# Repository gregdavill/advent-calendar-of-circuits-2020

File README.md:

# Advent Calendar of Circuits 2020 #

## What is it?
The challenge is to design an average of 1 circuit board design and layout per day for 31 days in December.

## Designs

  1. [__gdpi__](gpdi/) SYZYGY pod featuring 2x digital video ports
  2. [__resonance__](resonance/) Addon board for card10 to add video output
  3. [__meiji-led-ring__](meiji-led-ring/) Illuminator to fit around the front of a microscope
  4. [__pcie_x4__](pcie_x4/) SYZYGY pod creating a PCIe x4 add-in card
  5. [__icebreaker++__](icebreaker++/) icebreaker FPGA board, upgraded with an ECP5
  6. [__pcie_x1__](pcie_x1/) SYZYGY pod creating a compact PCIe x1 add-in card
  7. [__arm-watch__](arm-watch/) New ARM based controller for the Casio CA-53W watch
  8. [__syzygy-sgmii__](syzygy-sgmii/) Gigabit ethernet using an SGMII based PHY
  9. [__hdmi-si__](hdmi-si/) HDMI breakout board
  10. [__quad-7segment__](pmod-quad-7segment/) PMOD with a quad 7segment
  11. [__syzygy-breakout__](syzygy-breakout/) Breakout board for a standard SYZYGY connector
  12. [__icebreaker++-ram__](icebreaker++-ram/) icebreaker FPGA board, upgraded with an ECP5 (+extra RAM)
  13. [__sd-dummy__](pmod-sd-dummy/) Dummy SD card to connect to a host system via SDIO
  14. [__gpdi-serdes__](gpdi-serdes/) GPDI using the serdes
  15. [__rpi-hq-camera__](rpi-hq-camera/) Connector for the Raspberry Pi HQ camera
  16. [__syzygy-pmod__](syzygy-pmod/) SYZYGY to PMOD adapter
  17. [__pmod-gnss__](pmod-gnss/) GNSS PMOD, GPS + Glonass
  18. [__led-panel__](led-panel/) Breakout for some White LEDs
  19. [__syzygy-txr-breakout__](syzygy-txr-breakout/) SYZYGY TXR4 to SMA connectors
  20. [__syzygy-dual-atto320__](syzygy-dual-atto320/) SYZYGY to dual Atto320 LWIR sensors
  21. [__syzygy-rgb888-lcd__](syzygy-rgb888-lcd/) SYZYGY 5" 800x480 LCD panel
  22. [__memory-lcd-wing__](memory-lcd-wing/) minimal wing for OrangeCrab
  23. [__syzygy-flir-tau2__](syzygy-flir-tau2/) SYZYGY tau2 LWIR core
  24. [__syzygy-flir-boson__](syzygy-flir-boson/) SYZYGY boson LWIR core
  25. [__SCD30-3d-model__](SCD30-3d-model/) 3d model for the SCD30 CO2 Sensor
  26. [__esp32s2-co2-monitor__](esp32s2-co2-monitor/) ESP32s2 + Sharp memory LCD + CO2 Monitor
  27. [__jtag-programmer__](jtag-programmer/) FT232H based JTAG programmer
  28. [__ECPBreaker__](ecpbreaker/) ECP5 based icebreaker update, FX2 HS USB + SYZYGY
  29. [__esp32s2-lepton__](esp32s2-lepton/) Small ESP32 based thermal camera
  30. [__esp32s2-breakout__](esp32s2-breakout/) ESP32S2 + Sharp memory LCD
  31. [__syzygy-epc901__](syzygy-epc901/) SYZYGY breakout with an EPC901 CCD + 50MSps ADC

## Licence
 * Unless otherwise indicated hardware in this repository is licensed under CERN-OHL-P-2.0

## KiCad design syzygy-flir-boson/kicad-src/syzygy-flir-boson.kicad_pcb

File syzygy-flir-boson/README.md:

# SYZYGY FLIR Boson 

SYZYGY is an FPGA expansion standard for medium to high speed interfaces. Learn more and check out the specifications here: [https://syzygyfpga.io/](https://syzygyfpga.io/)

---

## What is it

An addon for the boson LWIR core from FLIR. 
The 24bit CMOS channel is connected through to the SYZYGY connector along with the UART configuration channel.

## Folder structure

```
kicad-src: KiCad v6 source files
production:
 - Gerbers:      [project]_gerbers.zip
 - Schematic:    [project].pdf
 - Board render: [project].png
```

## Render

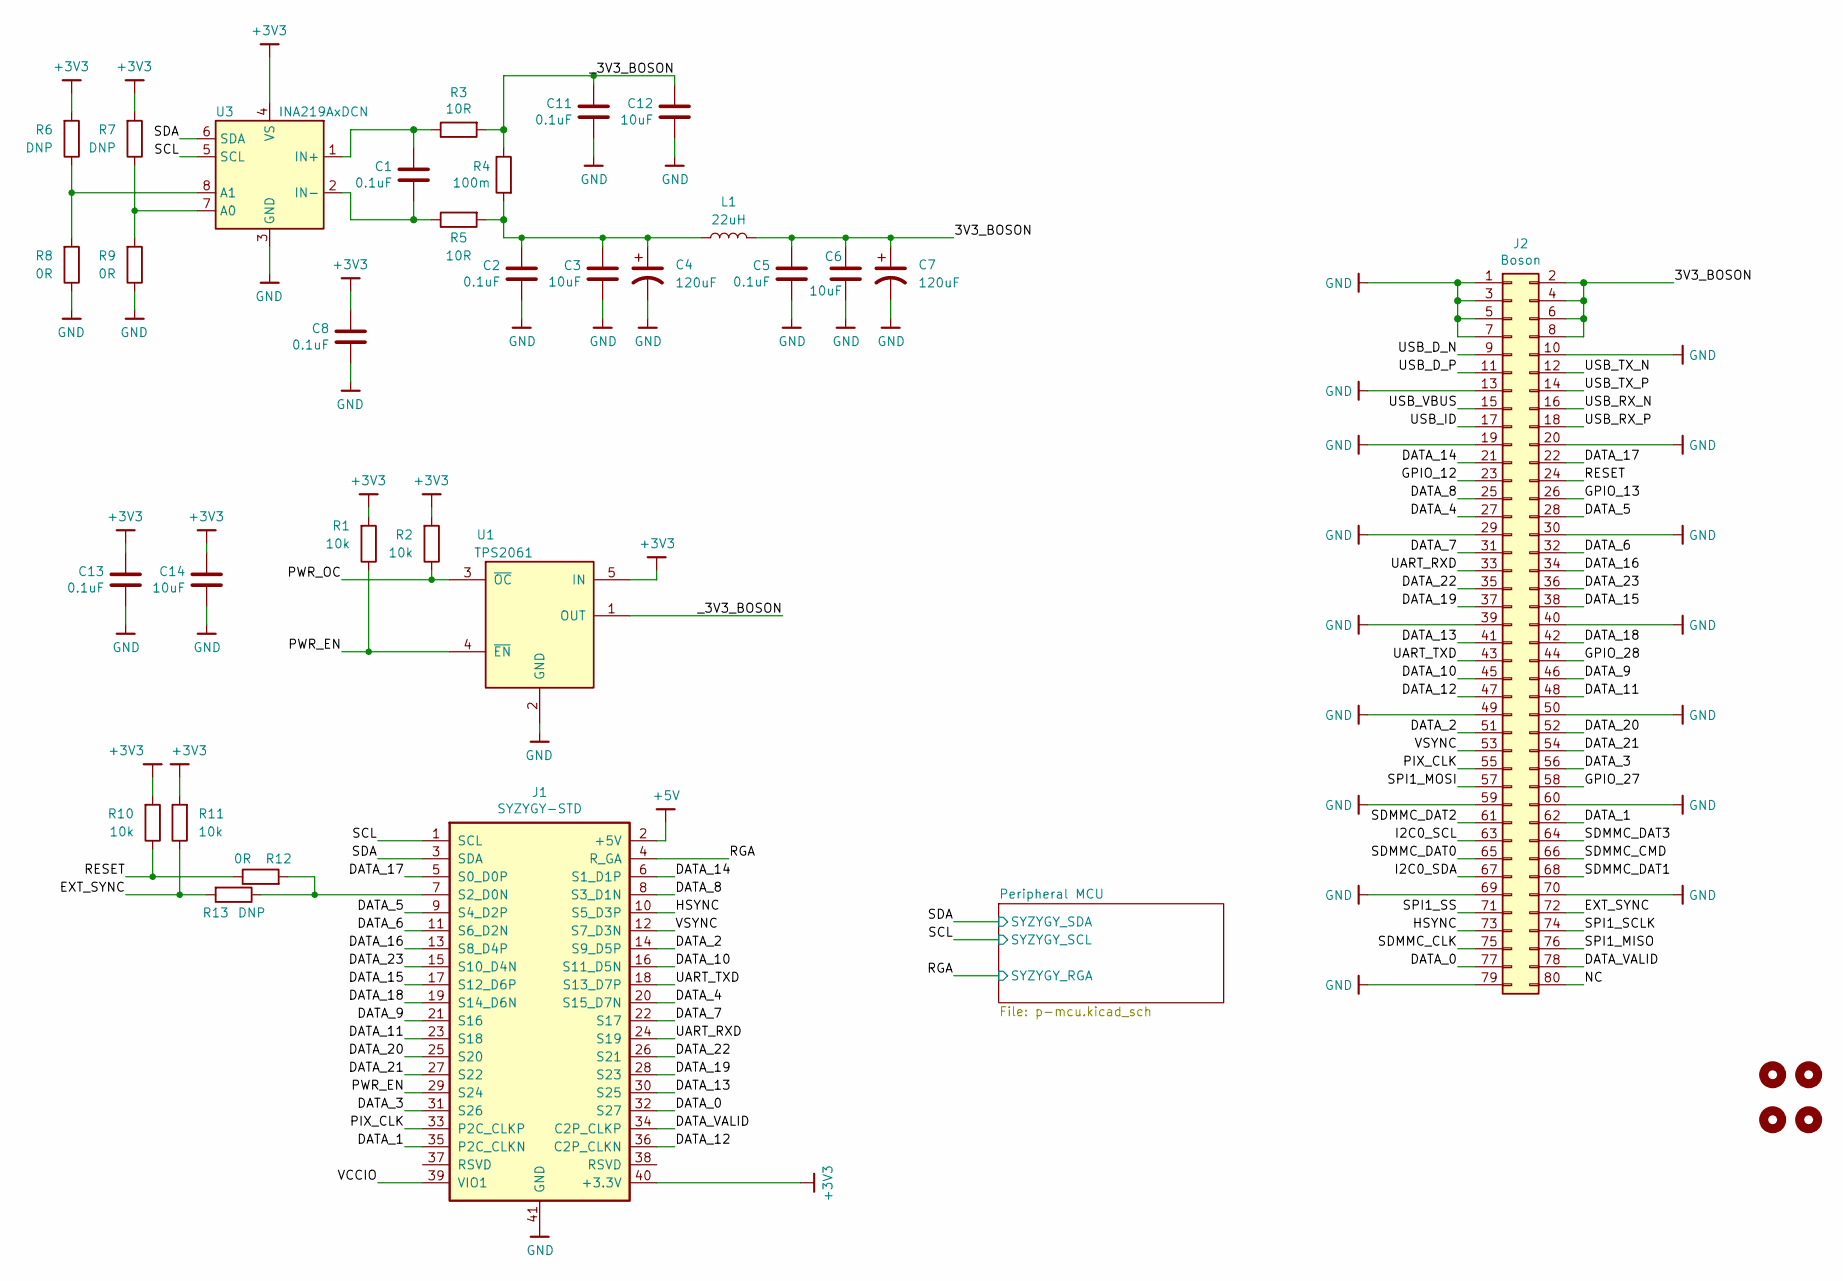
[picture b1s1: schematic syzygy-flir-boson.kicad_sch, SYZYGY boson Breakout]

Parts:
C1, C2, C5, C8, C11, C13: 0.1uF; C_0402_1005Metric
C3, C6, C12, C14: 10uF; C_0805_2012Metric
C4, C7: 120uF; CP_Elec_6.3x5.3
H1, H2, H3, H4: MountingHole; MountingHole_3.2mm_M3_DIN965
J1: SYZYGY-STD; SYZYGY-STD-POD
J2: Boson; DF40_80Pin
L1: 22uH; L_Taiyo-Yuden_NR-50xx
R1, R2, R10, R11: 10k; R_0402_1005Metric
R3, R5: 10R; R_0402_1005Metric
R4: 100m; R_0805_2012Metric
R6, R7, R13: DNP; R_0402_1005Metric
R8, R9, R12: 0R; R_0402_1005Metric
U1: TPS2061; SOT-23-5
U3: INA219AxDCN; SOT-23-8

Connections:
+3V3: C8.1, C13.1, C14.1, J1.40 (+3.3V), R1.2, R2.2, R6.2, R7.2, R10.2, R11.2, U1.5 (IN), U3.4 (VS); also elsewhere on the board
+5V: J1.2 (+5V)
/3V3_BOSON: C5.1, C6.1, C7.1, J2.2, J2.4, J2.6, J2.8, L1.2
/DATA_0: J1.32 (S27), J2.77
/DATA_1: J1.35 (P2C_CLKN), J2.62
/DATA_2: J1.14 (S9_D5P), J2.51
/DATA_3: J1.31 (S26), J2.56
/DATA_4: J1.20 (S15_D7N), J2.27
/DATA_5: J1.9 (S4_D2P), J2.28
/DATA_6: J1.11 (S6_D2N), J2.32
/DATA_7: J1.22 (S17), J2.31
/DATA_8: J1.8 (S3_D1N), J2.25
/DATA_9: J1.21 (S16), J2.46
/DATA_10: J1.16 (S11_D5N), J2.45
/DATA_11: J1.23 (S18), J2.48
/DATA_12: J1.36 (C2P_CLKN), J2.47
/DATA_13: J1.30 (S25), J2.41
/DATA_14: J1.6 (S1_D1P), J2.21
/DATA_15: J1.17 (S12_D6P), J2.38
/DATA_16: J1.13 (S8_D4P), J2.34
/DATA_17: J1.5 (S0_D0P), J2.22
/DATA_18: J1.19 (S14_D6N), J2.42
/DATA_19: J1.28 (S23), J2.37
/DATA_20: J1.25 (S20), J2.52
/DATA_21: J1.27 (S22), J2.54
/DATA_22: J1.26 (S21), J2.35
/DATA_23: J1.15 (S10_D4N), J2.36
/DATA_VALID: J1.34 (C2P_CLKP), J2.78
/EXT_SYNC: J2.72, R11.1, R13.2
/GPIO_12: J2.23
/GPIO_13: J2.26
/GPIO_27: J2.58
/GPIO_28: J2.44
/HSYNC: J1.10 (S5_D3P), J2.73
/I2C0_SCL: J2.63
/I2C0_SDA: J2.67
/NC: J2.80
/PIX_CLK: J1.33 (P2C_CLKP), J2.55
/PWR_EN: J1.29 (S24), R1.1, U1.4 (~EN)
/PWR_OC: R2.1, U1.3 (~OC)
/RESET: J2.24, R10.1, R12.1
/RGA: J1.4 (R_GA); also elsewhere on the board
/SCL: J1.1 (SCL), U3.5 (SCL); also elsewhere on the board
/SDA: J1.3 (SDA), U3.6 (SDA); also elsewhere on the board
/SDMMC_CLK: J2.75
/SDMMC_CMD: J2.66
/SDMMC_DAT0: J2.65
/SDMMC_DAT1: J2.68
/SDMMC_DAT2: J2.61
/SDMMC_DAT3: J2.64
/SPI1_MISO: J2.76
/SPI1_MOSI: J2.57
/SPI1_SCLK: J2.74
/SPI1_SS: J2.71
/UART_RXD: J1.24 (S19), J2.33
/UART_TXD: J1.18 (S13_D7P), J2.43
/USB_D_N: J2.9
/USB_D_P: J2.11
/USB_ID: J2.17
/USB_RX_N: J2.16
/USB_RX_P: J2.18
/USB_TX_N: J2.12
/USB_TX_P: J2.14
/USB_VBUS: J2.15
/VCCIO: J1.39 (VIO1)
/VSYNC: J1.12 (S7_D3N), J2.53
/_3V3_BOSON: C11.1, C12.1, R3.2, R4.1, U1.1 (OUT)
GND: C2.2, C3.2, C4.2, C5.2, C6.2, C7.2, C8.2, C11.2, C12.2, C13.2, C14.2, J1.41 (GND), J2.1, J2.3, J2.5, J2.7, J2.10, J2.13, J2.19, J2.20, J2.29, J2.30, J2.39, J2.40, J2.49, J2.50, J2.59, J2.60, J2.69, J2.70, J2.79, R8.1, R9.1, U1.2 (GND), U3.3 (GND); also elsewhere on the board
unnamed: C1.1, R3.1, U3.1 (IN+)
unnamed: C1.2, R5.1, U3.2 (IN-)
unnamed: C2.1, C3.1, C4.1, L1.1, R4.2, R5.2
unnamed: J1.7 (S2_D0N), R12.2, R13.1
unnamed: R6.1, R8.2, U3.8 (A1)
unnamed: R7.1, R9.2, U3.7 (A0)

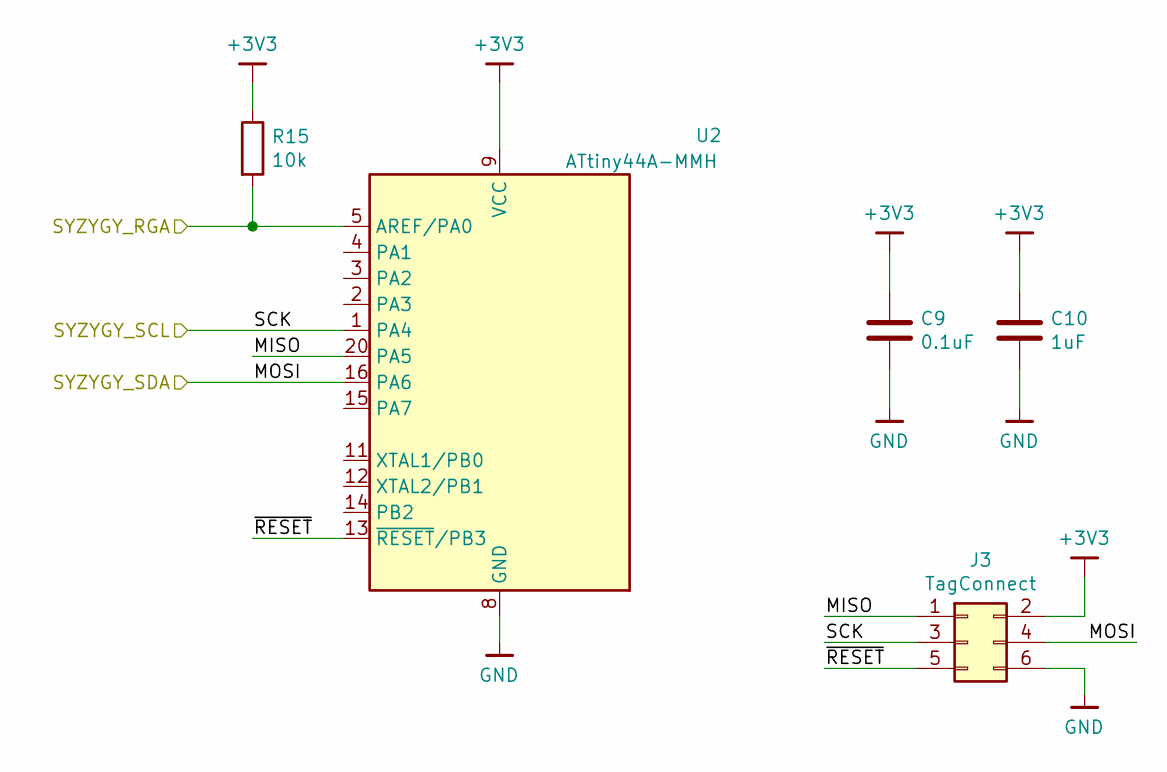
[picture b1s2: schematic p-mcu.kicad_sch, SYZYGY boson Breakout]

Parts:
C9: 0.1uF; C_0402_1005Metric
C10: 1uF; C_0402_1005Metric
J3: TagConnect; TC2030-NL_SMALL
R15: 10k; R_0402_1005Metric
U2: ATtiny44A-MMH; QFN-20-1EP_3x3mm_P0.45mm_EP1.6x1.6mm

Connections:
+3V3: C9.1, C10.1, J3.2, R15.1, U2.9 (VCC); also elsewhere on the board
/Peripheral MCU/MISO: J3.1, U2.20 (PA5)
/Peripheral MCU/~RESET: J3.5, U2.13 (~RESET~/PB3)
/RGA: R15.2, U2.5 (AREF/PA0); also elsewhere on the board
/SCL: J3.3, U2.1 (PA4); also elsewhere on the board
/SDA: J3.4, U2.16 (PA6); also elsewhere on the board
GND: C9.2, C10.2, J3.6, U2.8 (GND), U2.21 (GND); also elsewhere on the board

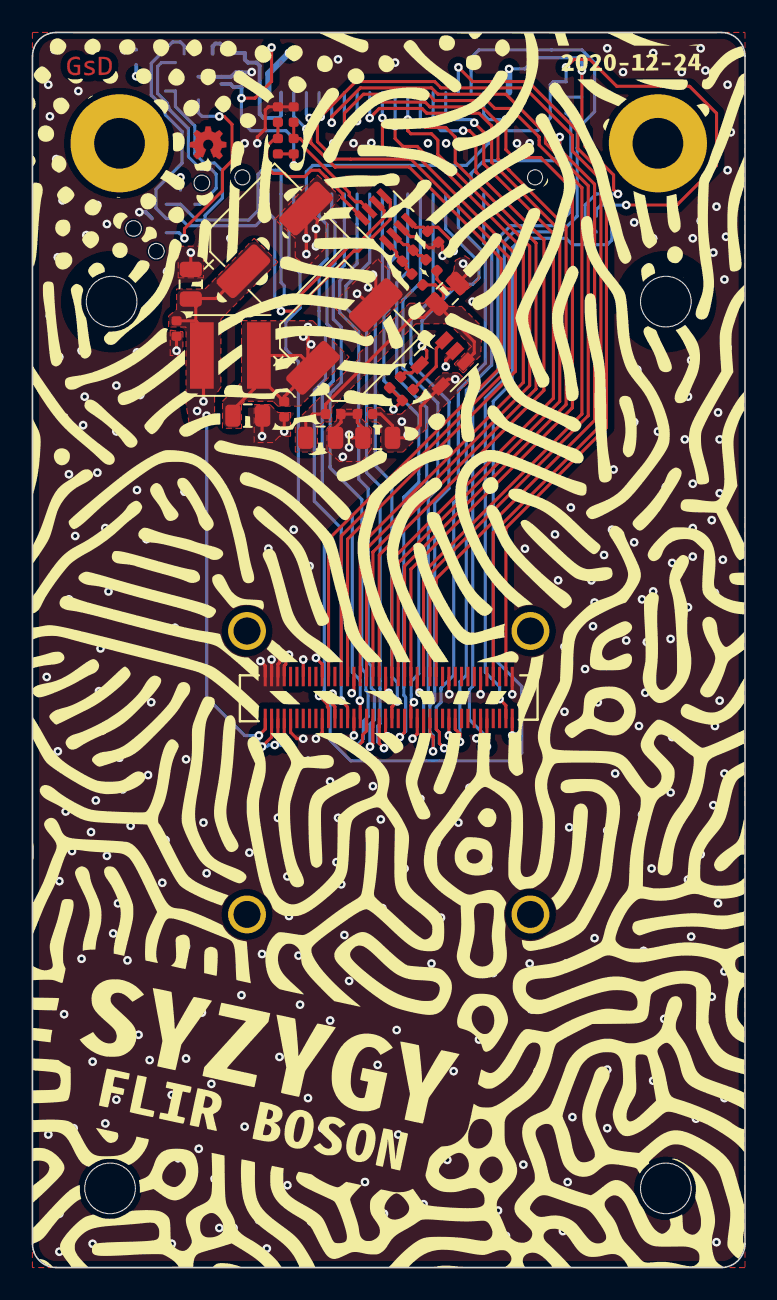
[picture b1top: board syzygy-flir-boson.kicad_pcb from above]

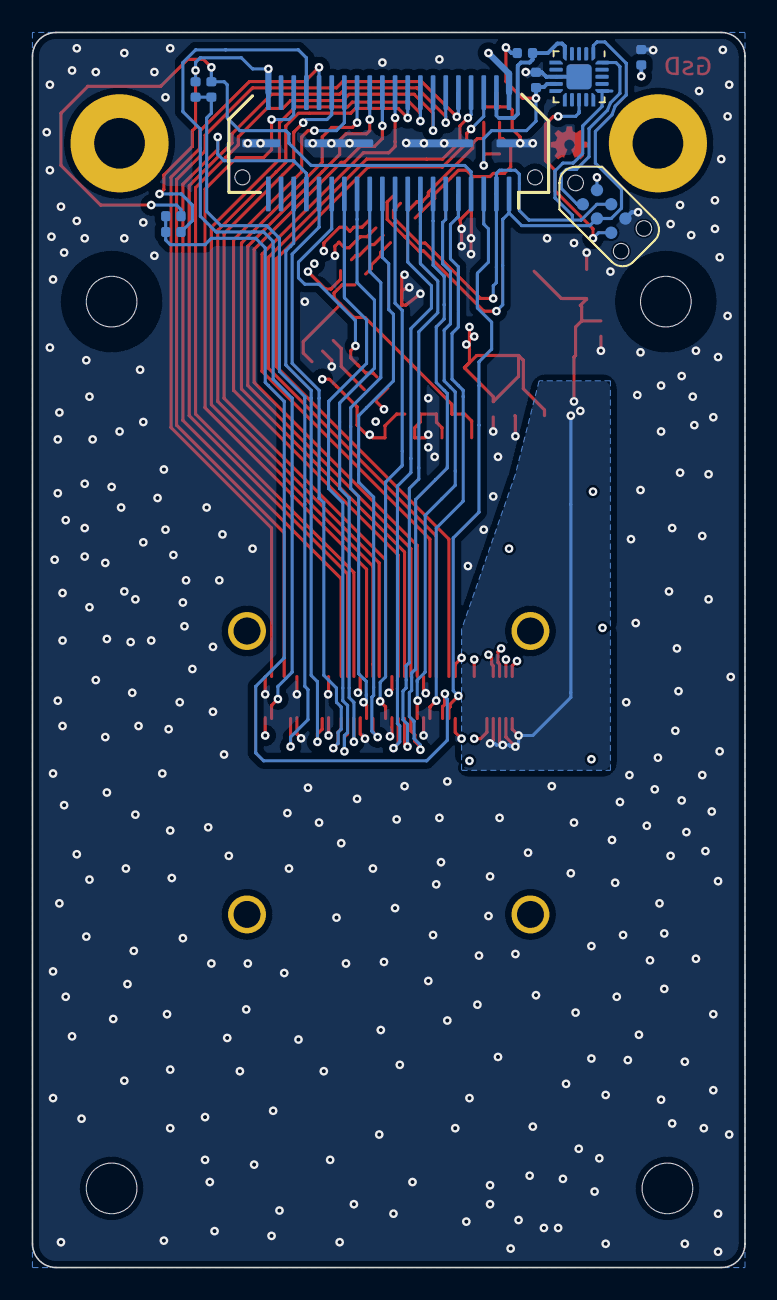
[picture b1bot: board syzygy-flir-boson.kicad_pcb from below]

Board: 4 copper layers, 45.0 x 78.0 mm, 43 parts (10 on the bottom side), 49 nets.

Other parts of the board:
H1#2: MountingHole; MountingHole_3.2mm_M3_DIN965
H1#3, H1#4, H1#5: MountingHole; Pin_D1.0mm_L10.0mm

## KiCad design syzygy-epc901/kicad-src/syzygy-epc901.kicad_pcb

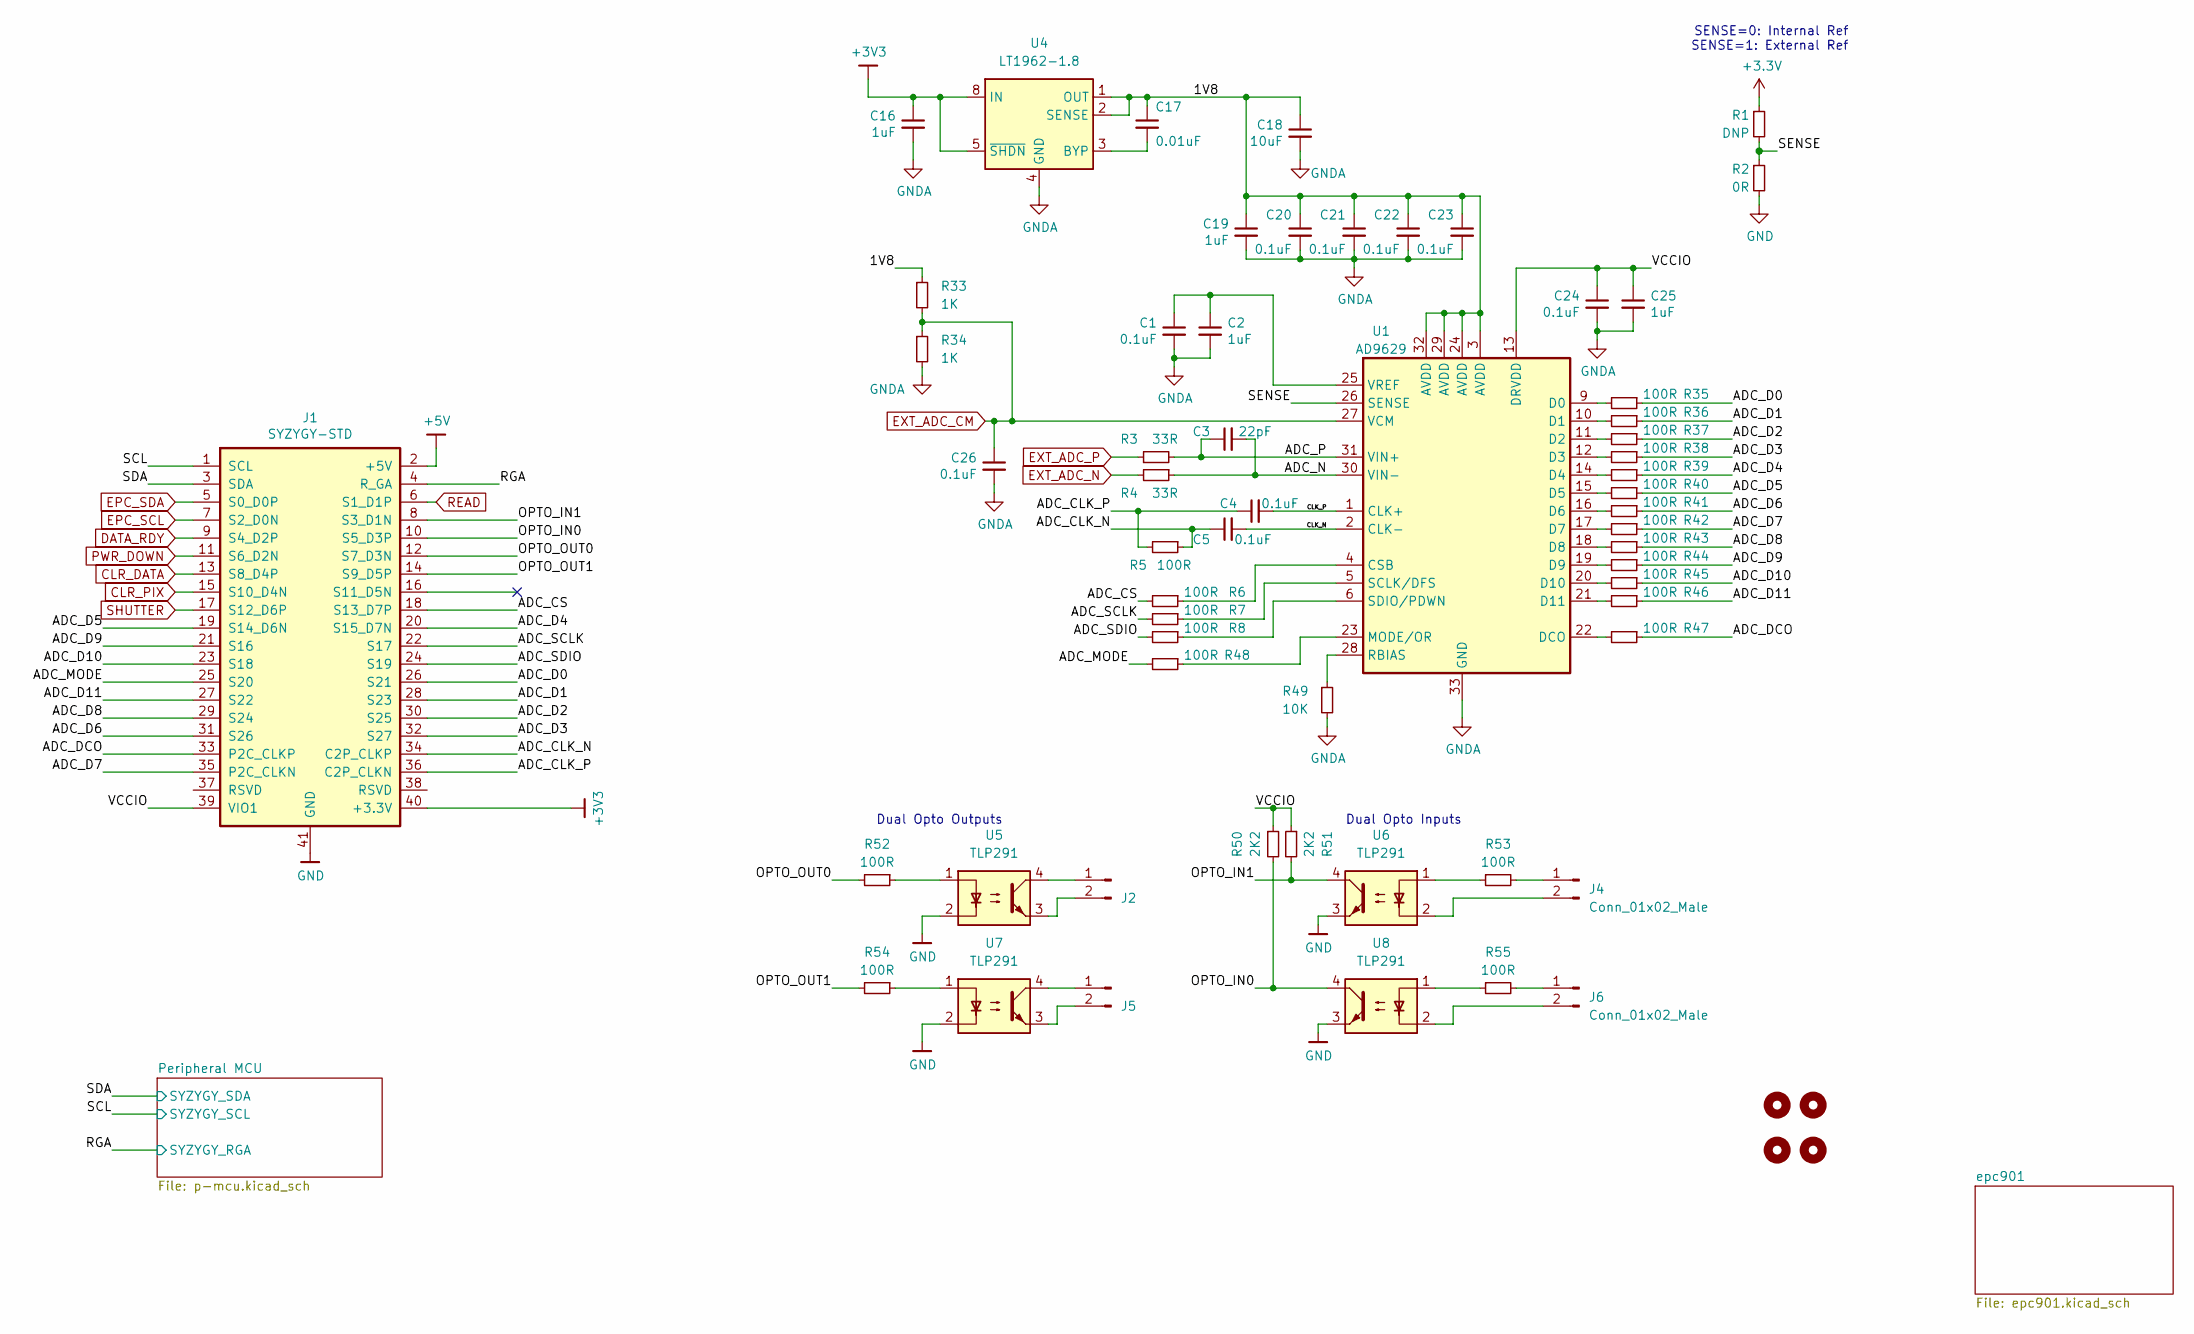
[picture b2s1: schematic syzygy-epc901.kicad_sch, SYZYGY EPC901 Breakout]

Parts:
C1, C4, C5, C20, C21, C22, C23, C24, C26: 0.1uF; C_0402_1005Metric
C2, C16, C19, C25: 1uF; C_0402_1005Metric
C3: 22pF; C_0402_1005Metric
C17: 0.01uF; C_0402_1005Metric
C18: 10uF; C_0603_1608Metric
H1, H2, H3, H4: MountingHole; MountingHole_3.2mm_M3_DIN965
J1: SYZYGY-STD; SYZYGY-STD-POD
J2, J4, J5, J6: Conn_01x02_Male; PinHeader_1x02_P2.54mm_Vertical
R1: DNP; R_0402_1005Metric
R2: 0R; R_0402_1005Metric
R3, R4: 33R; R_0402_1005Metric
R5, R6, R7, R8, R35, R36, R37, R38, R39, R40, R41, R42, R43, R44, R45, R46, R47, R48, R52, R53, R54, R55: 100R; R_0402_1005Metric
R33, R34: 1K; R_0402_1005Metric
R49: 10K; R_0402_1005Metric
R50, R51: 2K2; R_0402_1005Metric
U1: AD9629; QFN-32-1EP_5x5mm_P0.5mm_EP3.6x3.6mm_ThermalVias
U4: LT1962-1.8; MSOP-8_3x3mm_P0.65mm
U5, U6, U7, U8: TLP291; SOIC-4_4.55x2.6mm_P1.27mm

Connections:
+5V: J1.2 (+5V)
/1V8: C17.1, C18.1, C19.1, C20.1, C21.1, C22.1, C23.1, R33.1, U1.3 (AVDD), U1.24 (AVDD), U1.29 (AVDD), U1.32 (AVDD), U4.1 (OUT), U4.2 (SENSE)
/ADC_CLK_N: C5.1, J1.34 (C2P_CLKP), R5.1
/ADC_CLK_P: C4.1, J1.36 (C2P_CLKN), R5.2
/ADC_CS: J1.18 (S13_D7P), R6.2
/ADC_D0: J1.26 (S21), R35.1
/ADC_D1: J1.28 (S23), R36.1
/ADC_D2: J1.30 (S25), R37.1
/ADC_D3: J1.32 (S27), R38.1
/ADC_D4: J1.20 (S15_D7N), R39.1
/ADC_D5: J1.19 (S14_D6N), R40.1
/ADC_D6: J1.31 (S26), R41.1
/ADC_D7: J1.35 (P2C_CLKN), R42.1
/ADC_D8: J1.29 (S24), R43.1
/ADC_D9: J1.21 (S16), R44.1
/ADC_D10: J1.23 (S18), R45.1
/ADC_D11: J1.27 (S22), R46.1
/ADC_DCO: J1.33 (P2C_CLKP), R47.1
/ADC_MODE: J1.25 (S20), R48.2
/ADC_N: C3.2, R4.1, U1.30 (VIN-)
/ADC_P: C3.1, R3.2, U1.31 (VIN+)
/ADC_SCLK: J1.22 (S17), R7.2
/ADC_SDIO: J1.24 (S19), R8.2
/CLK_N: C5.2, U1.2 (CLK-)
/CLK_P: C4.2, U1.1 (CLK+)
/OPTO_IN0: J1.10 (S5_D3P), R50.2, U8.4
/OPTO_IN1: J1.8 (S3_D1N), R51.2, U6.4
/OPTO_OUT0: J1.12 (S7_D3N), R52.2
/OPTO_OUT1: J1.14 (S9_D5P), R54.2
/RGA: J1.4 (R_GA); also elsewhere on the board
/SCL: J1.1 (SCL); also elsewhere on the board
/SDA: J1.3 (SDA); also elsewhere on the board
/SENSE: R1.2, R2.1, U1.26 (SENSE)
/VCCIO: C24.1, C25.1, J1.39 (VIO1), R50.1, R51.1, U1.13 (DRVDD)
CLR_DATA: J1.13 (S8_D4P); also elsewhere on the board
CLR_PIX: J1.15 (S10_D4N); also elsewhere on the board
DATA_RDY: J1.9 (S4_D2P); also elsewhere on the board
EPC_SCL: J1.7 (S2_D0N); also elsewhere on the board
EPC_SDA: J1.5 (S0_D0P); also elsewhere on the board
EXT_ADC_CM: C26.1, R33.2, R34.1, U1.27 (VCM); also elsewhere on the board
EXT_ADC_N: R4.2; also elsewhere on the board
EXT_ADC_P: R3.1; also elsewhere on the board
GND: C1.2, C2.2, C16.2, C18.2, C19.2, C20.2, C21.2, C22.2, C23.2, C24.2, C25.2, C26.2, J1.41 (GND), R2.2, R34.2, R49.2, U1.33 (GND), U4.4 (GND), U5.2, U6.3, U7.2, U8.3; also elsewhere on the board
unnamed: C1.1, C2.1, U1.25 (VREF)
unnamed: C17.2, U4.3 (BYP)
unnamed: J2.1, U5.4
unnamed: J2.2, U5.3
unnamed: J4.1, R53.2
unnamed: J4.2, U6.2
unnamed: J5.1, U7.4
unnamed: J5.2, U7.3
unnamed: J6.1, R55.2
unnamed: J6.2, U8.2
unnamed: R6.1, U1.4 (CSB)
unnamed: R7.1, U1.5 (SCLK/DFS)
unnamed: R8.1, U1.6 (SDIO/PDWN)
unnamed: R35.2, U1.9 (D0)
unnamed: R36.2, U1.10 (D1)
unnamed: R37.2, U1.11 (D2)
unnamed: R38.2, U1.12 (D3)
unnamed: R39.2, U1.14 (D4)
unnamed: R40.2, U1.15 (D5)
unnamed: R41.2, U1.16 (D6)
unnamed: R42.2, U1.17 (D7)
unnamed: R43.2, U1.18 (D8)
unnamed: R44.2, U1.19 (D9)
unnamed: R45.2, U1.20 (D10)
unnamed: R46.2, U1.21 (D11)
unnamed: R47.2, U1.22 (DCO)
unnamed: R48.1, U1.23 (MODE/OR)
unnamed: R49.1, U1.28 (RBIAS)
unnamed: R52.1, U5.1
unnamed: R53.1, U6.1
unnamed: R54.1, U7.1
unnamed: R55.1, U8.1
PWR_DOWN: J1.11 (S6_D2N); also elsewhere on the board
READ: J1.6 (S1_D1P); also elsewhere on the board
SHUTTER: J1.17 (S12_D6P); also elsewhere on the board

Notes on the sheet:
Dual Opto Outputs
Dual Opto Inputs
SENSE=0: Internal Ref SENSE=1: External Ref

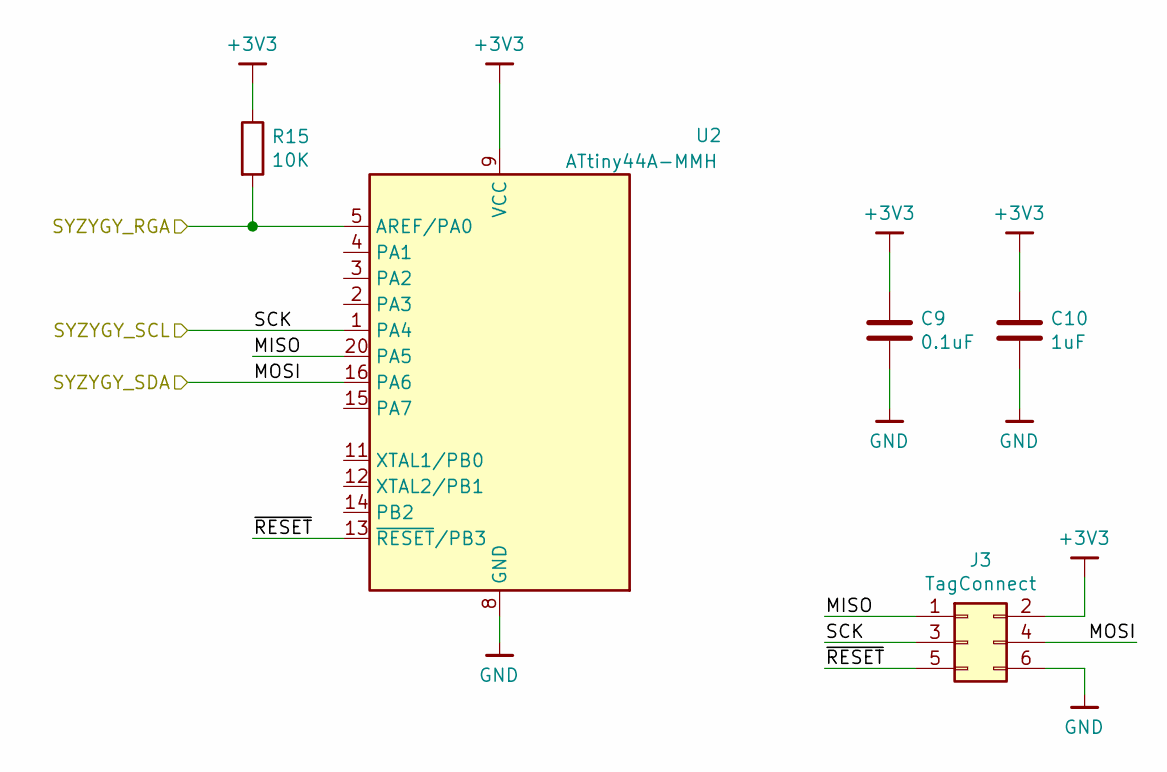
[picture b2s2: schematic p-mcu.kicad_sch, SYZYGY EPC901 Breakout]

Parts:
C9: 0.1uF; C_0402_1005Metric
C10: 1uF; C_0402_1005Metric
J3: TagConnect; TC2030-NL_SMALL
R15: 10K; R_0402_1005Metric
U2: ATtiny44A-MMH; QFN-20-1EP_3x3mm_P0.45mm_EP1.6x1.6mm

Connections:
/Peripheral MCU/MISO: J3.1, U2.20 (PA5)
/Peripheral MCU/~RESET: J3.5, U2.13 (~RESET~/PB3)
/RGA: R15.2, U2.5 (AREF/PA0); also elsewhere on the board
/SCL: J3.3, U2.1 (PA4); also elsewhere on the board
/SDA: J3.4, U2.16 (PA6); also elsewhere on the board
GND: C9.2, C10.2, J3.6, U2.8 (GND), U2.21 (GND); also elsewhere on the board

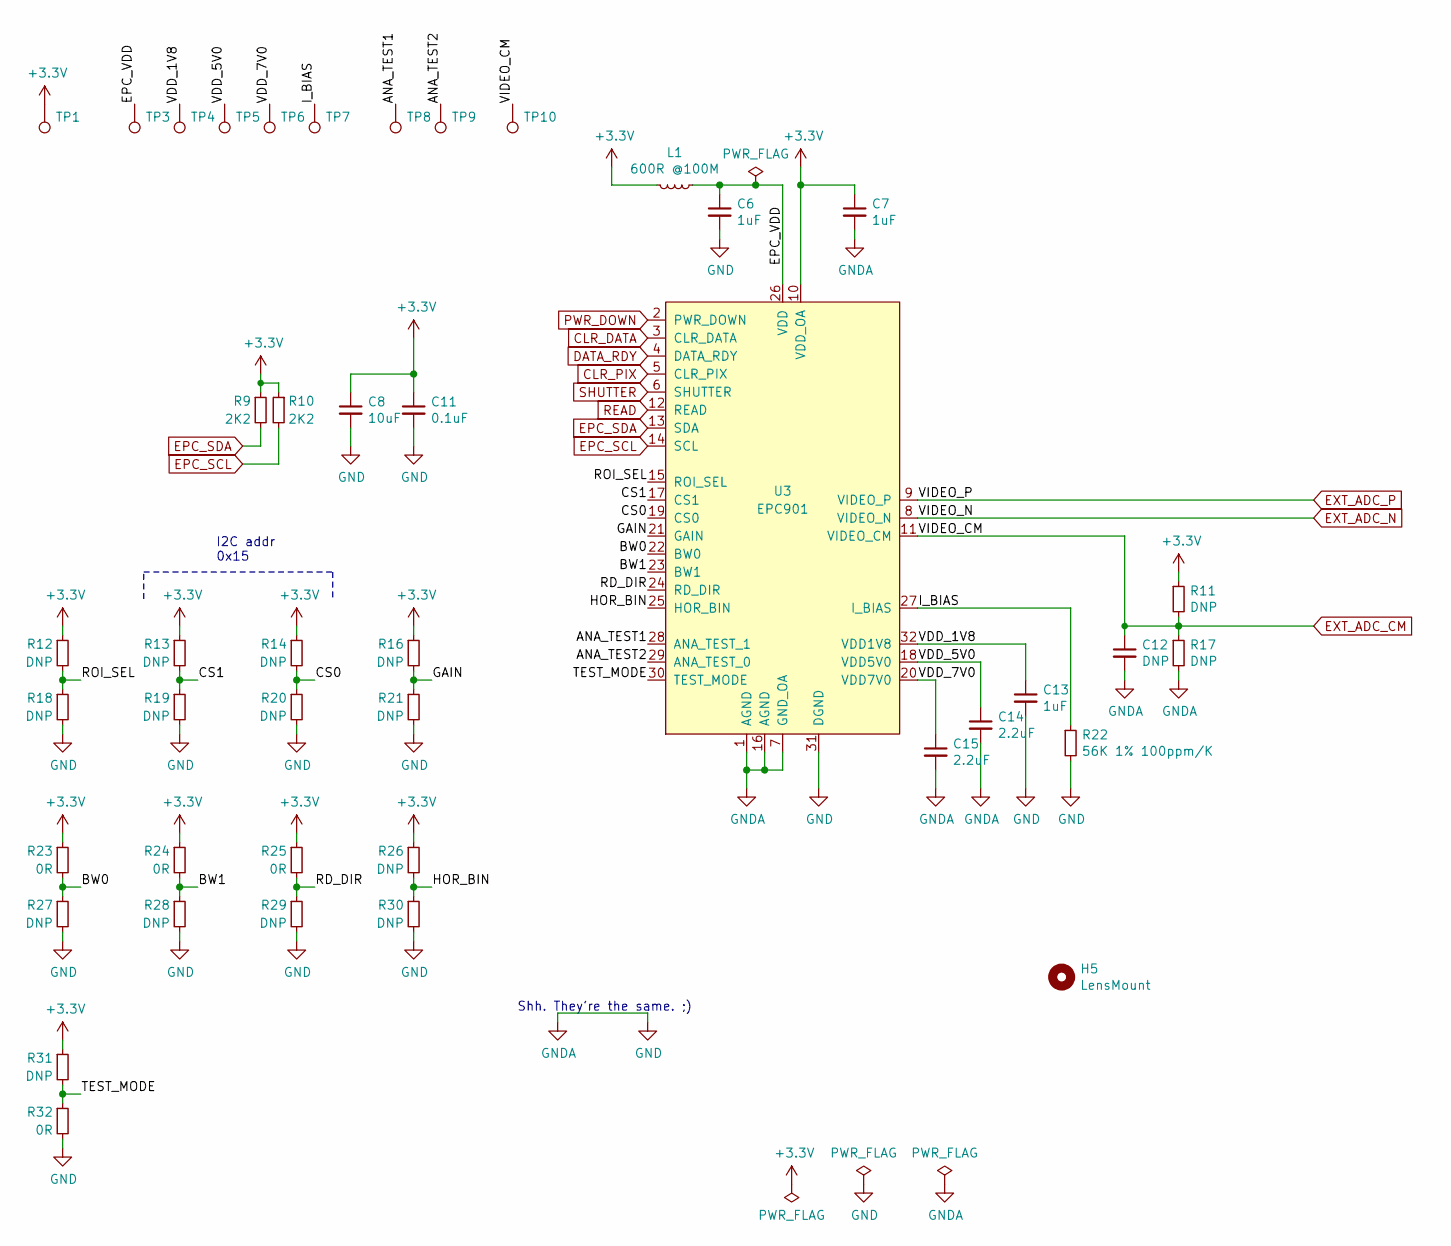
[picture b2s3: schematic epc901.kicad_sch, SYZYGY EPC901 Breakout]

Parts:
C6, C7, C13: 1uF; C_0402_1005Metric
C8: 10uF; C_0603_1608Metric
C11: 0.1uF; C_0402_1005Metric
C12: DNP; C_0402_1005Metric
C14, C15: 2.2uF; C_0402_1005Metric
H5: LensMount; lensholder-m12-20mm
L1: 600R @100M; L_0402_1005Metric
R9, R10: 2K2; R_0402_1005Metric
R11, R12, R13, R14, R16, R17, R18, R19, R20, R21, R26, R27, R28, R29, R30, R31: DNP; R_0402_1005Metric
R22: 56K 1% 100ppm/K; R_0402_1005Metric
R23, R24, R25, R32: 0R; R_0402_1005Metric
TP1, TP3, TP4, TP5, TP6, TP7, TP8, TP9, TP10: TestPoint; TestPoint_Pad_D1.0mm
U3: EPC901; epc901

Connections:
/epc901/ANA_TEST1: TP8.1, U3.28 (ANA_TEST_1)
/epc901/ANA_TEST2: TP9.1, U3.29 (ANA_TEST_0)
/epc901/BW0: R23.2, R27.1, U3.22 (BW0)
/epc901/BW1: R24.2, R28.1, U3.23 (BW1)
/epc901/CS0: R14.2, R20.1, U3.19 (CS0)
/epc901/CS1: R13.2, R19.1, U3.17 (CS1)
/epc901/EPC_VDD: C6.1, L1.1, TP3.1, U3.26 (VDD)
/epc901/GAIN: R16.2, R21.1, U3.21 (GAIN)
/epc901/HOR_BIN: R26.2, R30.1, U3.25 (HOR_BIN)
/epc901/I_BIAS: R22.1, TP7.1, U3.27 (I_BIAS)
/epc901/RD_DIR: R25.2, R29.1, U3.24 (RD_DIR)
/epc901/ROI_SEL: R12.2, R18.1, U3.15 (ROI_SEL)
/epc901/TEST_MODE: R31.2, R32.1, U3.30 (TEST_MODE)
/epc901/VDD_1V8: C13.1, TP4.1, U3.32 (VDD1V8)
/epc901/VDD_5V0: C14.1, TP5.1, U3.18 (VDD5V0)
/epc901/VDD_7V0: C15.1, TP6.1, U3.20 (VDD7V0)
CLR_DATA: U3.3 (CLR_DATA); also elsewhere on the board
CLR_PIX: U3.5 (CLR_PIX); also elsewhere on the board
DATA_RDY: U3.4 (DATA_RDY); also elsewhere on the board
EPC_SCL: R10.2, U3.14 (SCL); also elsewhere on the board
EPC_SDA: R9.2, U3.13 (SDA); also elsewhere on the board
EXT_ADC_CM: C12.1, R11.2, R17.1, TP10.1, U3.11 (VIDEO_CM); also elsewhere on the board
EXT_ADC_N: U3.8 (VIDEO_N); also elsewhere on the board
EXT_ADC_P: U3.9 (VIDEO_P); also elsewhere on the board
GND: C6.2, C7.2, C8.2, C11.2, C12.2, C13.2, C14.2, C15.2, R17.2, R18.2, R19.2, R20.2, R21.2, R22.2, R27.2, R28.2, R29.2, R30.2, R32.2, U3.1 (AGND), U3.7 (GND_OA), U3.16 (AGND), U3.31 (DGND); also elsewhere on the board
PWR_DOWN: U3.2 (PWR_DOWN); also elsewhere on the board
READ: U3.12 (READ); also elsewhere on the board
SHUTTER: U3.6 (SHUTTER); also elsewhere on the board

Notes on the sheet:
I2C addr 0x15
Shh. They're the same. ;)

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
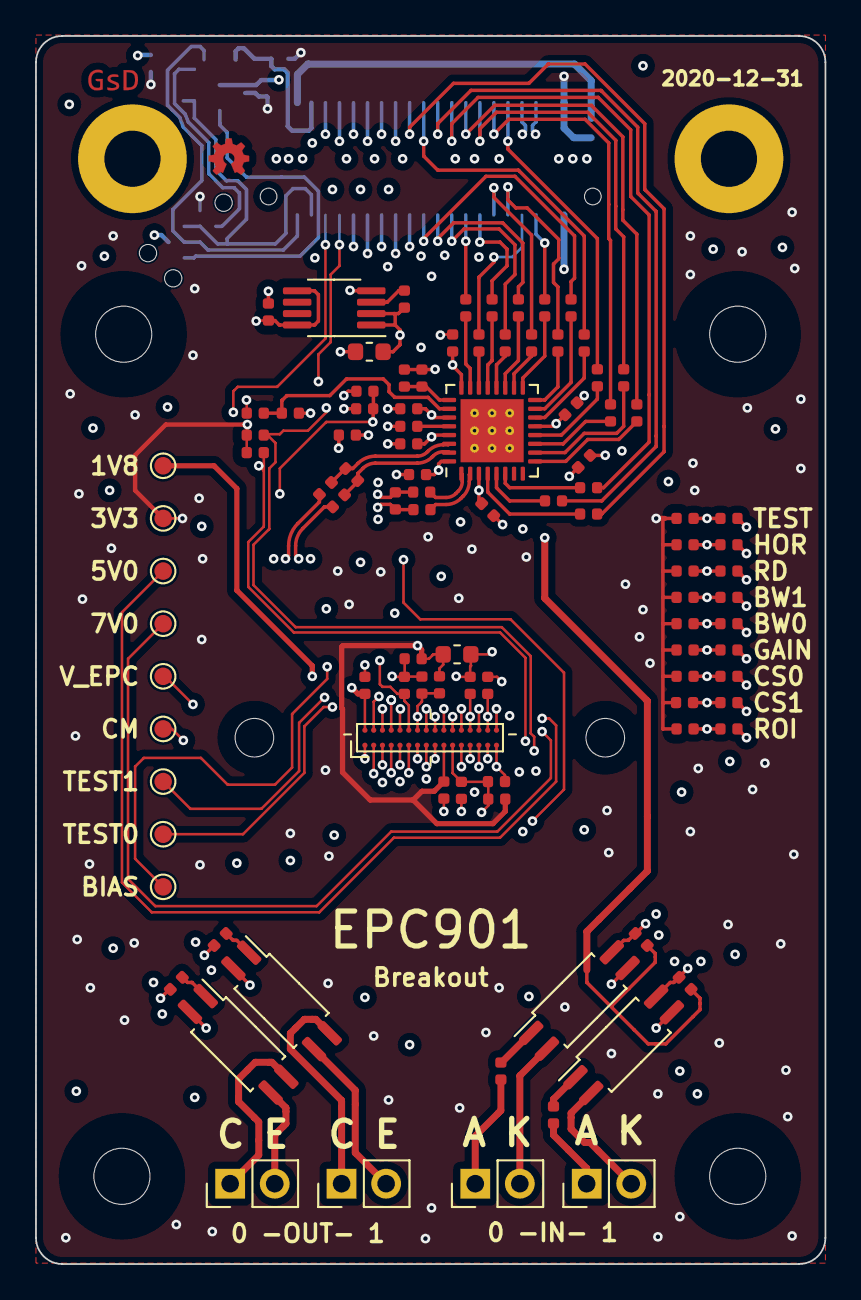
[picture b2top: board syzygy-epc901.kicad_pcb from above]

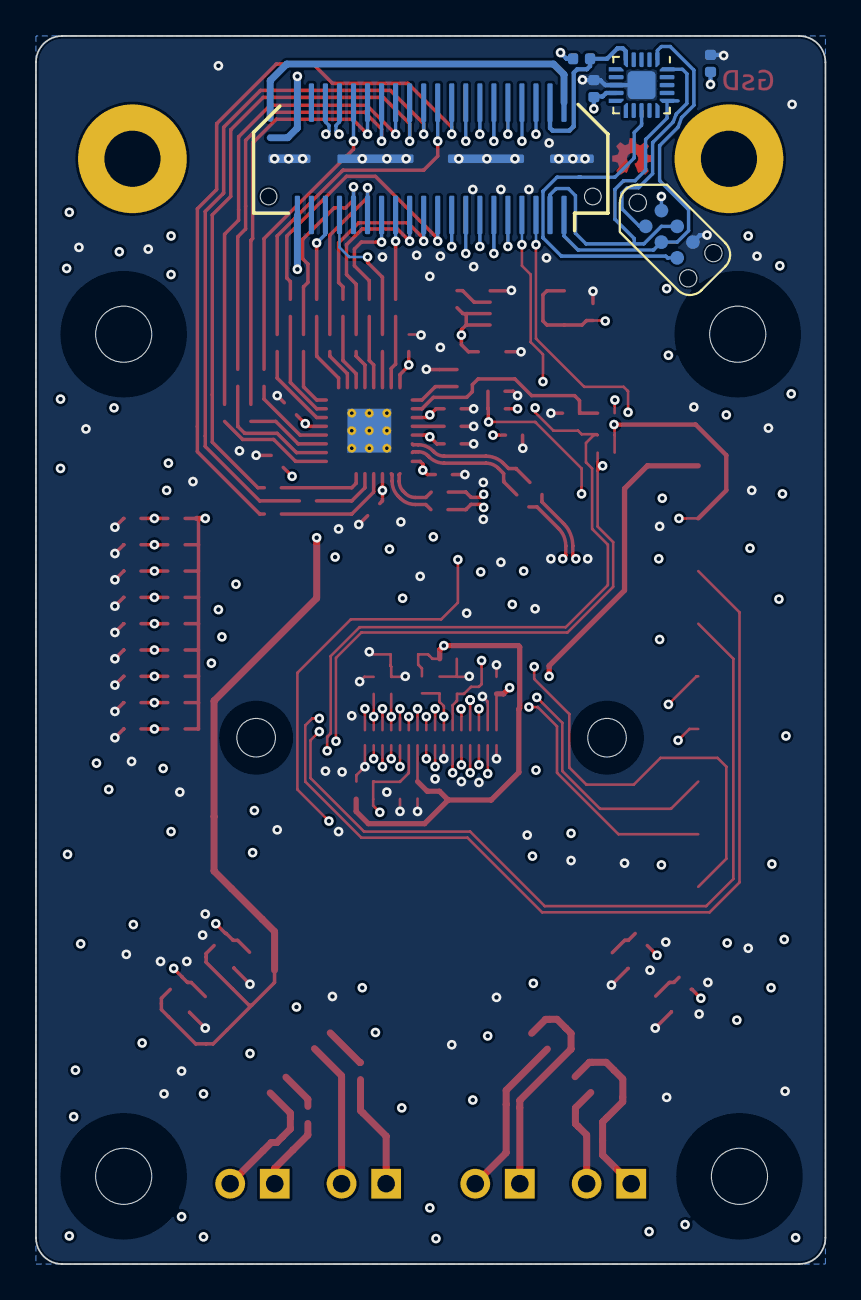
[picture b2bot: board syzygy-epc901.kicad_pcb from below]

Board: 4 copper layers, 45.0 x 70.0 mm, 110 parts (6 on the bottom side), 96 nets.
